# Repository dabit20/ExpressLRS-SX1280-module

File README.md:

# ExpressLRS SX1280-based Rx/Tx module

This module is a first shot at creating a suitable platform for a 2.4GHz port of the [ExpressLRS](https://github.com/AlessandroAU/ExpressLRS) radio link system for model aircraft.
It is based on the 20x20 M2 flight stack form factor and it uses the Chengdu EByte E28 modules, which are available in +12dBm, +20dBm and +27dBm output power. All these modules should work

This PCB can be used in the JR bay as the TX module, and on the quadcopter (or other RC aircraft) as RX module. Check the ExpressLRS project for more details. 

The board has not been tested yet. Beware.

Design was done in KiCAD 5.1 
Production files, PDF and artist impressions are available in the production_data/ directory

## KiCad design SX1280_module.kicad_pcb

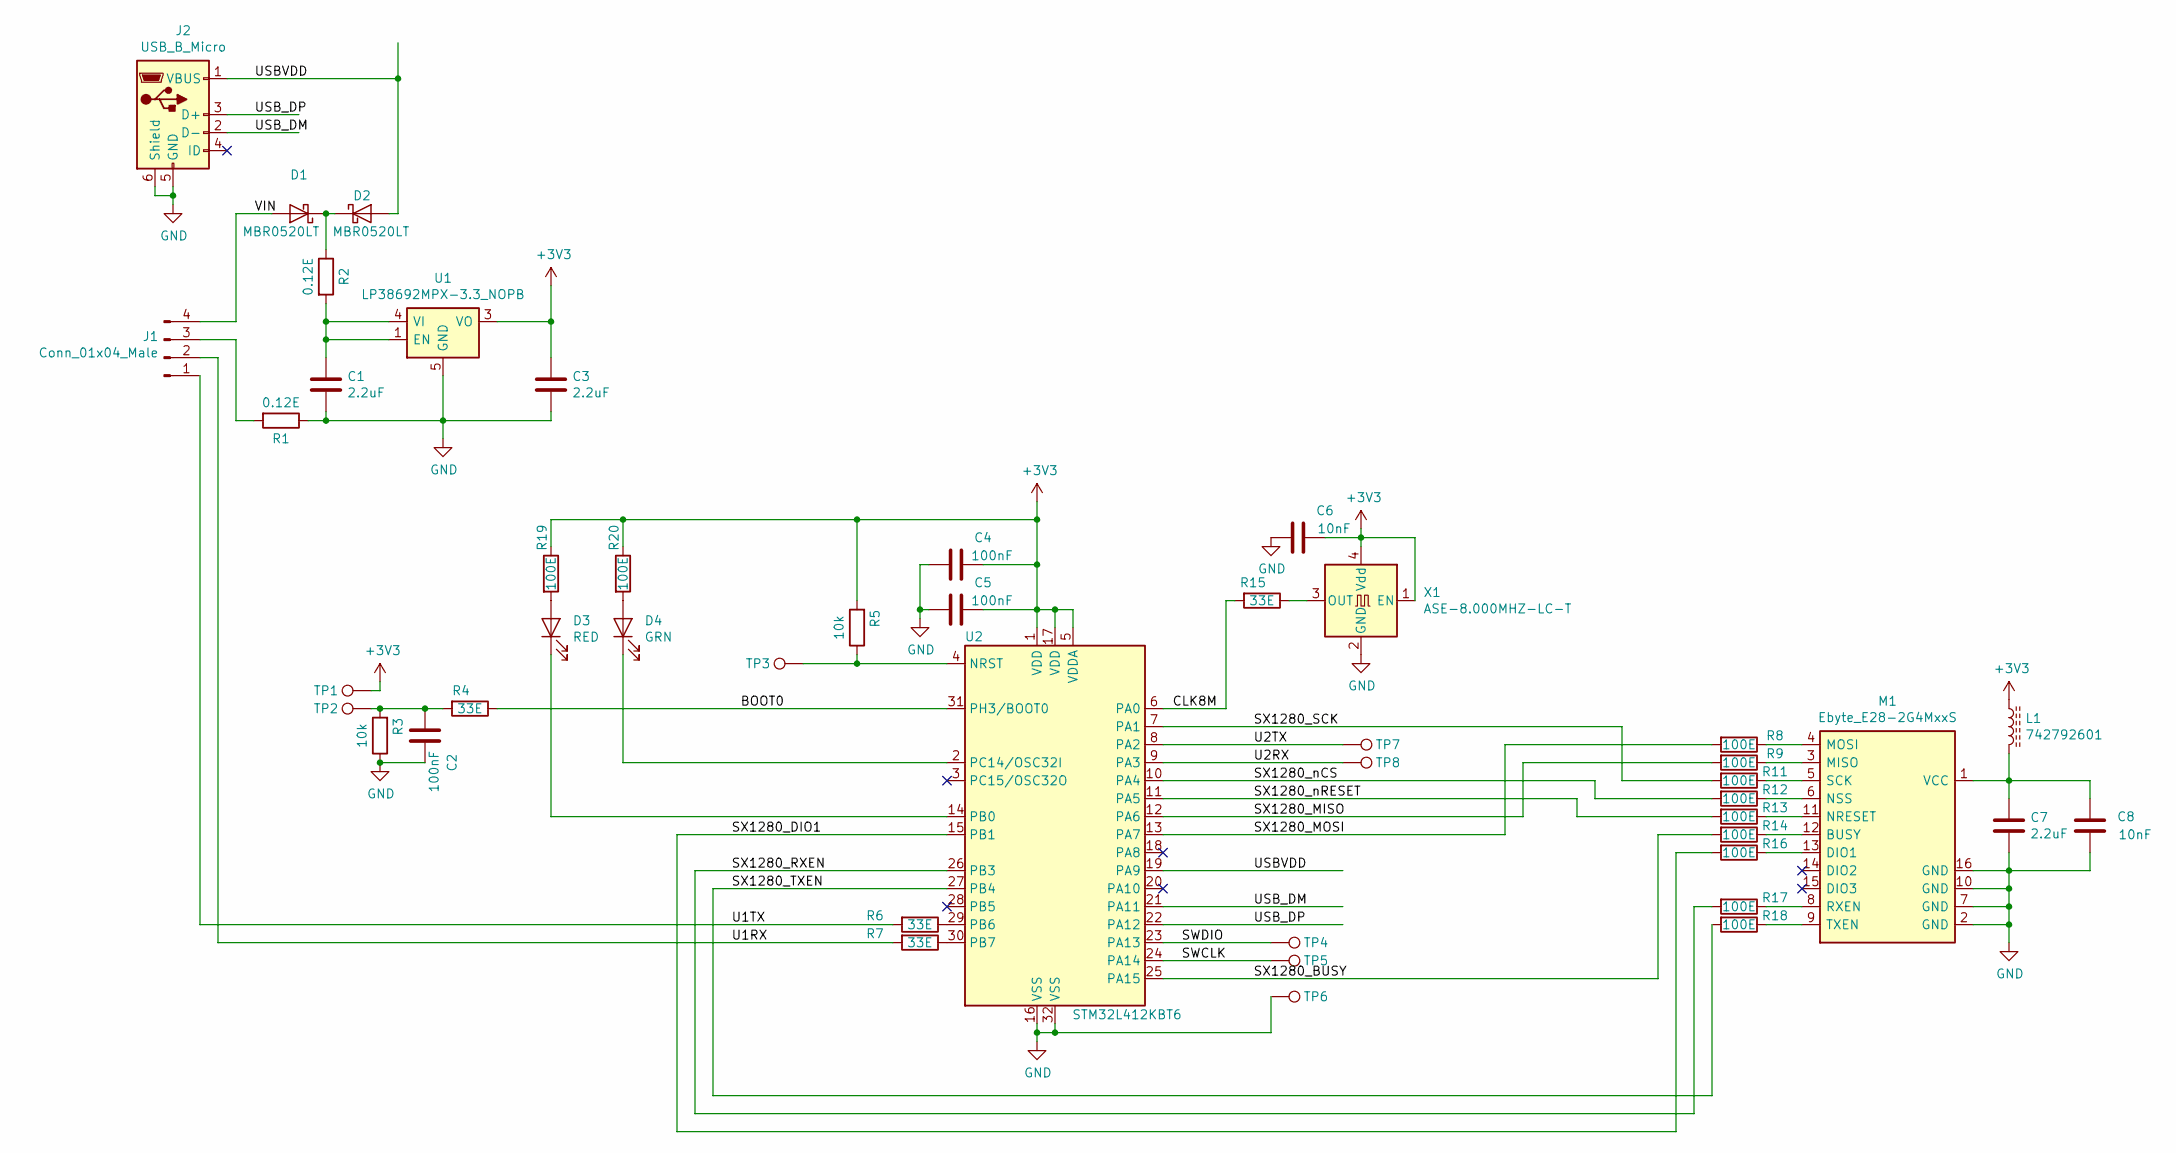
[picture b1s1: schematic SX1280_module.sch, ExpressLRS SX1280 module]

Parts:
C1, C3, C7: 2.2uF; C_0603_1608Metric; Manufacturer_PN Any
C2, C4, C5: 100nF; C_0603_1608Metric; Manufacturer_PN Any
C6, C8: 10nF; C_0603_1608Metric; Manufacturer_PN Any
D1, D2: MBR0520LT; D_SOD-123; Manufacturer_PN MBR0520LT
D3: RED; LED_0603_1608Metric; Manufacturer_PN KP-1608EC
D4: GRN; LED_0603_1608Metric; Manufacturer_PN KPT-1608SGC
J1: Conn_01x04_Male; PinHeader_1x04_P2.00mm_Vertical; Manufacturer_PN Any
J2: USB_B_Micro; USB_Micro-B_Wuerth_614105150721_Vertical_CircularHoles; Manufacturer_PN 614105150721
L1: 742792601; L_0603_1608Metric; Manufacturer_PN 742792601
M1: Ebyte_E28-2G4MxxS; E28-2G4MxxS; Manufacturer_PN E28-2G4M20S
R1, R2: 0.12E; R_0603_1608Metric; Manufacturer_PN Any
R3, R5: 10k; R_0603_1608Metric; Manufacturer_PN Any
R4, R6, R7, R15: 33E; R_0603_1608Metric; Manufacturer_PN Any
R8, R9, R11, R12, R13, R14, R16, R17, R18, R19, R20: 100E; R_0603_1608Metric; Manufacturer_PN Any
TP1, TP2, TP3, TP4, TP5, TP6, TP7, TP8: TestPoint; TestPoint_Pad_D1.0mm; Manufacturer_PN Not Applicable
U1: LP38692MPX-3.3_NOPB; SOT-223-5; Manufacturer_PN LP38692MPX-3.3_NOPB
U2: STM32L412KBT6; LQFP-32_7x7mm_P0.8mm; Manufacturer_PN STM32L412KBT6; DIGIKEY_PARTNR 497-18229-ND
X1: ASE-8.000MHZ-LC-T; Oscillator_SMD_Abracon_ASE-4Pin_3.2x2.5mm; Manufacturer_PN ASE-8.000MHZ-LC-T

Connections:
+3V3: C3.1, C4.1, C5.1, C6.1, L1.1, R5.2, R19.1, R20.1, TP1.1, U1.3 (VO), U2.1 (VDD), U2.5 (VDDA), U2.17 (VDD), X1.1 (EN), X1.4 (Vdd)
/BOOT0: R4.1, U2.31 (PH3/BOOT0)
/CLK8M: R15.2, U2.6 (PA0)
/SWCLK: TP5.1, U2.24 (PA14)
/SWDIO: TP4.1, U2.23 (PA13)
/SX1280_BUSY: R14.2, U2.25 (PA15)
/SX1280_DIO1: R16.2, U2.15 (PB1)
/SX1280_MISO: R9.2, U2.12 (PA6)
/SX1280_MOSI: R8.2, U2.13 (PA7)
/SX1280_RXEN: R17.2, U2.26 (PB3)
/SX1280_SCK: R11.2, U2.7 (PA1)
/SX1280_TXEN: R18.2, U2.27 (PB4)
/SX1280_nCS: R12.2, U2.10 (PA4)
/SX1280_nRESET: R13.2, U2.11 (PA5)
/U1RX: J1.2, R7.2
/U1TX: J1.1, R6.2
/U2RX: TP8.1, U2.9 (PA3)
/U2TX: TP7.1, U2.8 (PA2)
/USBVDD: D2.2 (A), J2.1 (VBUS), U2.19 (PA9)
/USB_DM: J2.2 (D-), U2.21 (PA11)
/USB_DP: J2.3 (D+), U2.22 (PA12)
/VIN: D1.2 (A), J1.4
GND: C1.2, C2.1, C3.2, C4.2, C5.2, C6.2, C7.2, C8.1, J2.5 (GND), J2.6 (Shield), M1.2 (GND), M1.7 (GND), M1.10 (GND), M1.16 (GND), R1.1, R3.1, TP6.1, U1.5 (GND), U2.16 (VSS), U2.32 (VSS), X1.2 (GND)
unnamed: C1.1, R2.2, U1.1 (EN), U1.4 (VI)
unnamed: C2.2, R3.2, R4.2, TP2.1
unnamed: C7.1, C8.2, L1.2, M1.1 (VCC)
unnamed: D1.1 (K), D2.1 (K), R2.1
unnamed: D3.1 (K), U2.14 (PB0)
unnamed: D3.2 (A), R19.2
unnamed: D4.1 (K), U2.2 (PC14/OSC32I)
unnamed: D4.2 (A), R20.2
unnamed: J1.3, R1.2
unnamed: M1.3 (MISO), R9.1
unnamed: M1.4 (MOSI), R8.1
unnamed: M1.5 (SCK), R11.1
unnamed: M1.6 (NSS), R12.1
unnamed: M1.8 (RXEN), R17.1
unnamed: M1.9 (TXEN), R18.1
unnamed: M1.11 (NRESET), R13.1
unnamed: M1.12 (BUSY), R14.1
unnamed: M1.13 (DIO1), R16.1
unnamed: R5.1, TP3.1, U2.4 (NRST)
unnamed: R6.1, U2.29 (PB6)
unnamed: R7.1, U2.30 (PB7)
unnamed: R15.1, X1.3 (OUT)

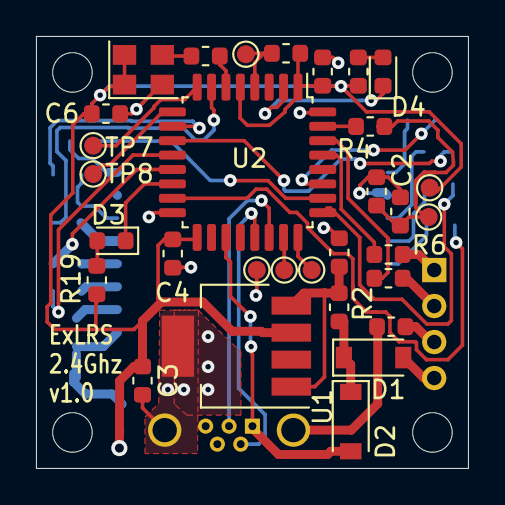
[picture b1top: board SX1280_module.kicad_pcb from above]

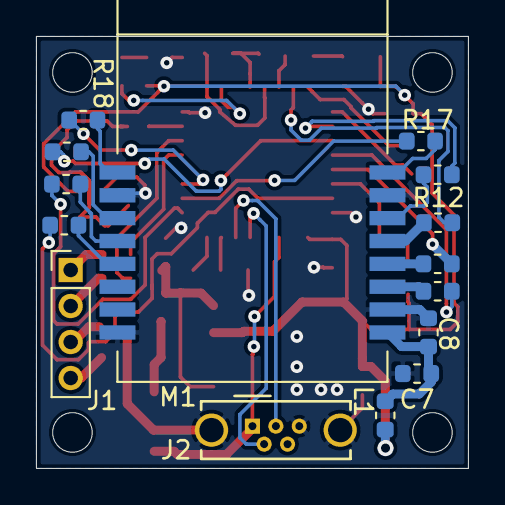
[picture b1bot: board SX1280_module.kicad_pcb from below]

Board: 2 copper layers, 24.0 x 24.0 mm, 50 parts (15 on the bottom side), 45 nets.

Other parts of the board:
MH1, MH1#2, MH2, MH2#2: MountingHole_2.2mm_M2_ISO7380
